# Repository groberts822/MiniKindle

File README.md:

# MiniKindle
A mini e-reader/kindle!
---
Final Design:

Final Build:

Demo:

https://youtube.com/shorts/sy03gHUxKEQ 

CAD Models:

Note for the CAD design. There are holes to connect the wires from the switch and TP4056 (the pos and neg) to the pins of the ESP32C3, its just hard to get a good picture of those. Also, the battery setup will be soldered to the 5V and GND pins of the microcontroller as the battery pads are covered by the case, and its simply easier to access the 5V pin, which works just fine as it can take the 3.7V down to the 3.3V fine.

Another note, the case will be assembled by using super glue to secure all 3D printed parts to one another. The PCB fits right into place and (should) fit securely enough to keep it in place without wiggling. 

Assembly:

Just a note, the eink display will be mounted to the board through the pins for the white connector. It may seem overly complicated, but i've done it for projects before and it's easier than it seems. It will simply be soldered from the pins there to the soldering holes using wires, as there isnt really an easier, compact way to connect it, and I just prefer this method.

Schematic:

PCB: 

3D of PCB with all Parts

Bill of Materials (also in .csv format)

| Item | Order Qty | Actual Amount Needed | Link |
|------|-----------|----------------------|------|
| Seeed Studio XIAO ESP32C3 | 1 | 1 | [Amazon](https://www.amazon.com/Seeed-Studio-XIAO-ESP32C3-Microcontroller/dp/B0B94JZ2YF/ref=sr_1_1_sspa?crid=25832RCF5SI0L&dib=eyJ2IjoiMSJ9.TUcu_JgOx4dykbtNXTKjde7ZwMAO9MNOl8WPl3lLjWA6_lh0zWqhFu8ssi_SoTl5KFVqyTZ9tAgb9PqizaJ32ZJKAd0hEp3TdaoLNJGKB1XUTIDDk0DZsTizZOOhf0xI46QUTnPtJs7RfaKayrCNN0LIqaFG8_6GSIPwPxTEhi2GGw4rubu_2GTfcJsvyHfB2icBKRNOjMpKD_wChiwkaBhNl56pvX0_OdoNT6kPr24N9x2JQELeAxxMpyM7SNXkSLPMREKSRGDVO3RT_nsXaD5XVOyTtIC9oOpkqvegOE4.Z5N7m13gSUHiz2zxnUHAEa4MM69LdYGM9WdJV3czJE8&dib_tag=se&keywords=esp32c3&qid=1773078950&s=electronics&sprefix=esp32c3%2Celectronics%2C210&sr=1-1-spons&sp_csd=d2lkZ2V0TmFtZT1zcF9hdGY&th=1) |
| Waveshare 2.13in E-Ink Display HAT | 1 | 1 | [Amazon](https://www.amazon.com/waveshare-2-13inch-HAT-Compatible-Resolution/dp/B071S8HT76/) |
| ANMBEST Micro SD Card Adapter | 1 pack (10pcs) | 1 | [Amazon](https://www.amazon.com/ANMBEST-Adapter-Interface-Conversion-Arduino/dp/B08CMLG4D6/) |
| DAOKI 6mm Tactile Push Buttons | 1 pack (100pcs) | 2 | [Amazon](https://www.amazon.com/DAOKI-Miniature-Momentary-Tactile-Quality/dp/B01CGMP9GY/) |
| MakerFocus 3.7V 1100mAh LiPo Battery | 1 pack (4pcs) | 1 | [Amazon](https://www.amazon.com/1100mAh-Rechargable-Protection-Insulated-Development/dp/B0867KDMY7/) |
| ALAMSCN TP4056 Type-C Charger | 1 pack (12pcs) | 1 | [Amazon](https://www.amazon.com/ALAMSCN-Lithium-Charging-Protection-Functions/dp/B08F7QSLN7/) |
| Mini Micro Slide Switch | 1 pack (20pcs) | 1 | [Amazon](https://www.amazon.com/Mini-Micro-Slide-Switch-Breadboard/dp/B0DN69L9SG/) |

------------------------------------------------------
I wanted a reading device which didn't feel like a smartphone. Most modern screens are meant to grab our attention with the backlight and notifications. This project is about the opposite, being a distraction-free and almost "offline" experience. This project uses an E-ink display and the text looks like actuasl paper and doesn't strain the eyes. Plus since the E-ink only uses power when the page changes initially, I can leave a book open for long periods of time without the battery dying. 

The brain of the project is a XIAO ESP32C3. When you flip the physical slide switch the system boots and reads the book files (.txt files) from the MicroSD card. There are 2 tactile buttons which allow you to essentially turn the page. It uses a 2.13-in electronic paper display (EPD) and is crisp in direct sunlight and stays on/displays text even after power is cut. A TP4056 module manages the 1100mAh LiPo battery, which you can charge via USB-C, and the slide switch makes sure the battery doesnt drain when the reader is not in use.

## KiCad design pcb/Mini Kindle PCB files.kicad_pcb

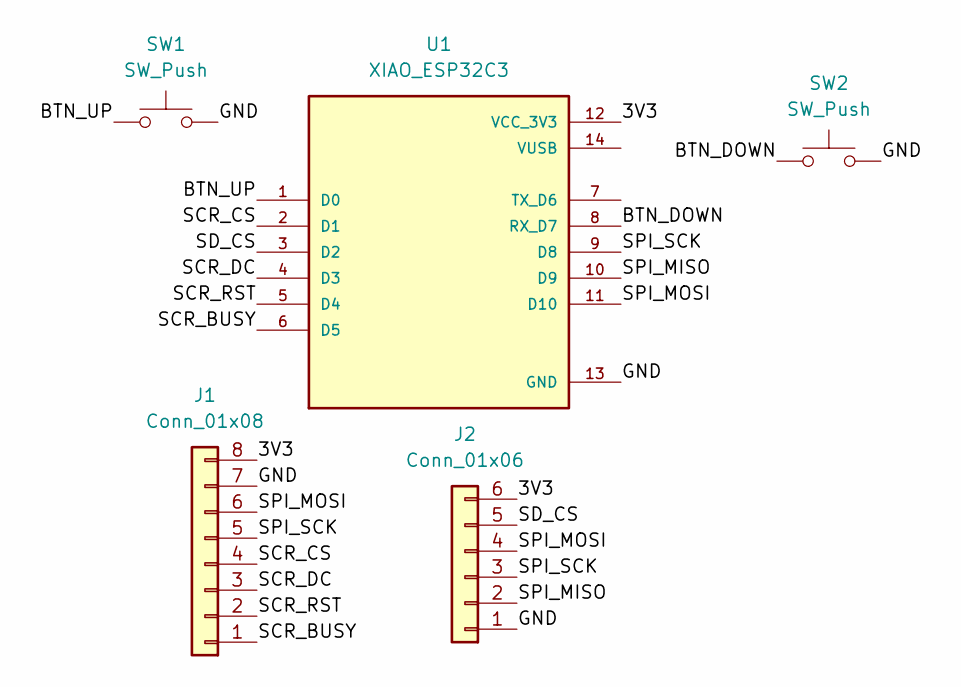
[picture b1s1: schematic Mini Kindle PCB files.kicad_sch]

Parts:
J1: Conn_01x08; PinHeader_1x08_P2.54mm_Vertical
J2: Conn_01x06; PinHeader_1x06_P2.54mm_Vertical
SW1, SW2: SW_Push; SW_PUSH_6mm
U1: XIAO_ESP32C3; MODULE_XIAO_ESP32C3; PARTREV 23/05/2022

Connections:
/3V3: J1.8, J2.6, U1.12 (VCC_3V3)
/BTN_DOWN: SW2.1, U1.8 (RX_D7)
/BTN_UP: SW1.1, U1.1 (D0)
/GND: J1.7, J2.1, SW1.2, SW2.2, U1.13 (GND)
/SCR_BUSY: J1.1, U1.6 (D5)
/SCR_CS: J1.4, U1.2 (D1)
/SCR_DC: J1.3, U1.4 (D3)
/SCR_RST: J1.2, U1.5 (D4)
/SD_CS: J2.5, U1.3 (D2)
/SPI_MISO: J2.2, U1.10 (D9)
/SPI_MOSI: J1.6, J2.4, U1.11 (D10)
/SPI_SCK: J1.5, J2.3, U1.9 (D8)

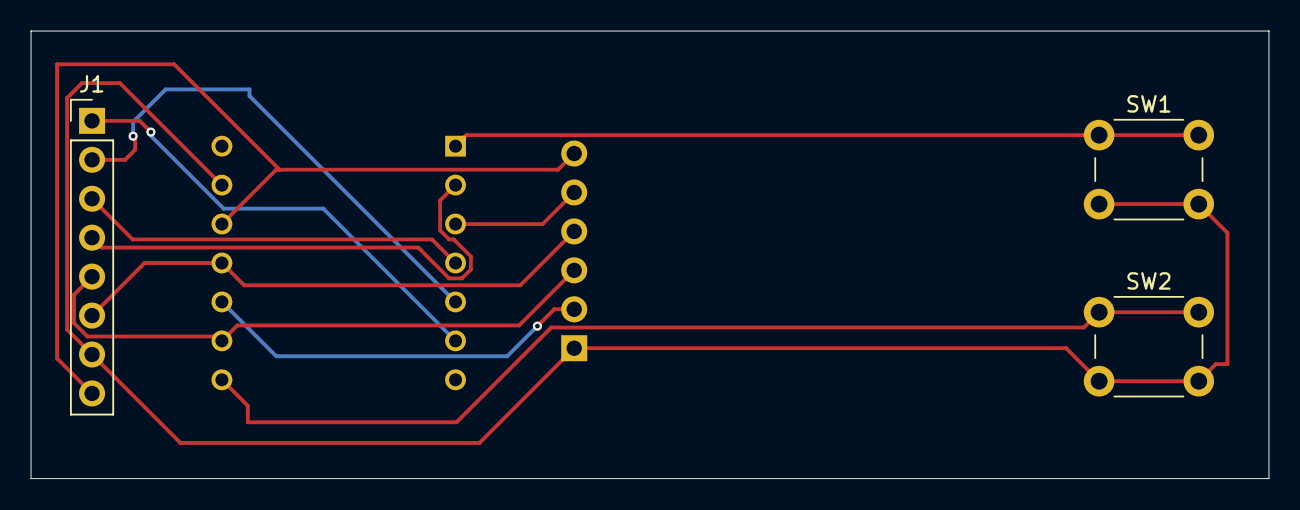
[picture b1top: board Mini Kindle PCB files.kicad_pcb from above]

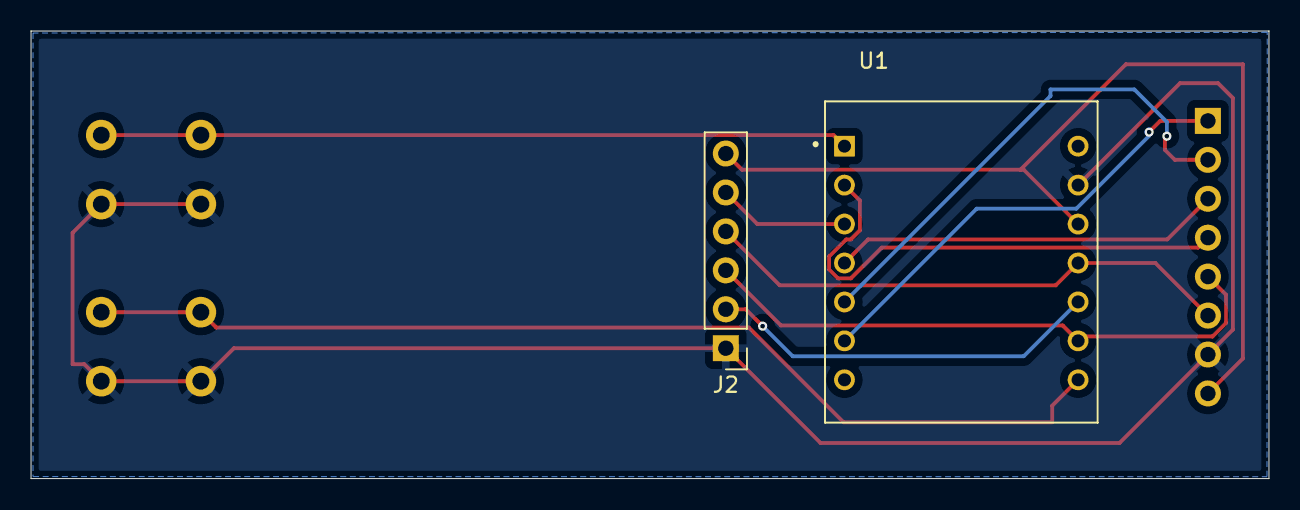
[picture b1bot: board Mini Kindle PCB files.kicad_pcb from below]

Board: 2 copper layers, 80.8 x 29.2 mm, 5 parts (2 on the bottom side), 12 nets.

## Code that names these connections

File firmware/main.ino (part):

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#define SCREEN_DC   5
#define SCREEN_RST  6
#define SCREEN_BUSY 7
#define SD_CS       4
#define SPI_MOSI    10
#define SPI_MISO    9
#define SPI_SCK     8
#define BTN_UP      2
#define BTN_DOWN    20

GxEPD2_BW<GxEPD2_213_BN, GxEPD2_213_BN::HEIGHT> display(
  GxEPD2_213_BN(SCREEN_CS, SCREEN_DC, SCREEN_RST, SCREEN_BUSY)
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void setup() {
  Serial.begin(115200);
  delay(300);
  pinMode(BTN_UP,   INPUT_PULLUP);
  pinMode(BTN_DOWN, INPUT_PULLUP);
  SPI.begin(SPI_SCK, SPI_MISO, SPI_MOSI);
  display.init(115200, true, 50, false);
  display.setRotation(3);
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
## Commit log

2026-02-22 Create 1
2026-03-15 Rename main.py to main.ino
